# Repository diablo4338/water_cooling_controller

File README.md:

# PC Water Cooling Controller

An end-to-end fan controller solution built around a custom PCB and an `ESP32-C3` controller. The repository covers the full product scope: device firmware, a desktop application for Windows and Linux, PCB manufacturing files, and the bill of materials.

The controller is designed for:
- up to 4 fans;
- up to 4 `10k` thermistors.

The desktop application works over BLE and supports pairing mode, controller connection, telemetry monitoring, and cooling parameter updates. The hardware lives in `hardware/`, and the release pipeline builds a unified set of artifacts through [`.github/workflows/release.yml`](.github/workflows/release.yml).

## Repository structure
- [`firmware/`](firmware/README.md) - `ESP-IDF` firmware for `ESP32-C3`.
- [`pcwcc/`](pcwcc/README.md) - desktop GUI for Windows and Linux.
- [`hardware/`](hardware/README.md) - KiCad project, BOM, and production exports for the PCB.
- [`tests/raspberry/`](tests/raspberry/README.md) - Raspberry Pi helper for hardware integration tests.
- [`docker/`](docker/README.md) - local Docker environment for release-build verification.
- [Architecture and documentation index](docs/architecture.md)

## Release artifacts
The `scripts/make_release.sh` script and the `Release` workflow produce:
- firmware for `ESP32-C3`;
- a Linux `AppImage` for the desktop client;
- a production archive with `Gerber` and `drill` files for PCB manufacturing;
- checksums;
- the BOM is stored separately in [`hardware/production/bom/main.csv`](hardware/production/bom/main.csv).

Build details and structure notes are kept in the `README` files of the corresponding directories.

## License

This project is licensed for non-commercial use only.

Commercial use is not permitted without prior written permission from the author.

See [LICENSE](LICENSE) for details.

## Safety disclaimer

This is an experimental DIY hardware/software project. Use it at your own risk.
Incorrect wiring, firmware, configuration, or installation may cause hardware
damage, overheating, fire, or injury.

See [DISCLAIMER.md](DISCLAIMER.md).

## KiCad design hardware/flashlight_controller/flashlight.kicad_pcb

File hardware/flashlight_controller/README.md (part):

# Flashlight controller — revision 1.1

Рабочий проект: `flashlight.kicad_pro`, схема `flashlight.kicad_sch`, плата
`flashlight.kicad_pcb`. Исходная версия сохранена в
`revision_backup_20260924.zip`. Монтаж снизу, питание 2S 6–8,4 В,
лампа около 1 А. Генераторы находятся в `tools/`.

## Повторное использование компонентов

Референс: `U:/plate_schemas/speed_and_temp_v8`, все восемь переданных файлов
доступны. Перечень компонентов всех листов сохранён в `tools/reference_parts.json`.
Скопированные посадочные места автономны: для повторной сборки проекта диск U:
не нужен.

| Здесь | Референс | Решение |
|---|---|---|
| U1 | esp U1 | Тот же ESP32-C3-WROOM-02 |
| U2 | fan_power U5 | Тот же MCP16331T-E/CH |
| U3 | power U2 | TPS7A02-3.3 (TPS7A0233PDBVR), SOT-23-5, как в референсе |
| C10, C11 | power C6, C5 | 1 мкФ на входе и 4,7 мкФ на выходе LDO, 0805 |
| U4 | ina U6 | Тот же INA226, корпус 3×3 мм с шагом 0,5 мм |
| Q1 | fan_power Q1 | MMFTP3334K вместо AO3401A, G1/S2/D3 |
| Q2 | fan_power Q2, esp Q3 | NXV40UNR вместо 2N7002, G1/S2/D3 |
| R1 | ina R17 | WSL2512R0470FEA, 47 мОм / 1% / 1 Вт |
| D1 | fan_power D2 | PD3S120LQ, скопировано посадочное место PowerDI323 |
| D2 | fan_power D3 | 1N4148WS-HG3_A-08 |
| SW1, SW2 | esp SW1–SW3 | Скопировано посадочное место кнопок |
| R2, R8 | fan_power R29, R34 | 61,9 кОм и 100 кОм из референса |
| R3–R6, R9–R16, R18 | разные листы | Повторно используются номиналы 1 кОм, 100 кОм, 10 Ом, 10 кОм, 4,7 кОм |
| C2–C7, C10, C12–C16 | разные листы | 100 нФ, 1 мкФ и 10 мкФ в 0805; напряжение и диэлектрик по BOM |

Новые номиналы: R7 523 кОм, R17 12,4 кОм. Сохранены конденсаторы 22 мкФ,
470 мкФ и дроссель 22 мкГн: они выбраны для этого источника и нагрузки.
SRN4018-100M из референса имеет 10 мкГн; без проверки устойчивости и пульсаций
его не подставляем вместо рекомендованных для 5 В 22 мкГн.
Установлен TPS7A02-3.3 из референса: IN и EN подключены к 5 В, NC оставлен
неподключённым. Его номинальный выходной ток — 200 мА; работу ESP32-C3 с радио
нужно проверить на прототипе по просадке 3,3 В. ADS1115 не требуется для
одного термодатчика. Разъёмы SATA и вентиляторов не соответствуют назначению платы.

## Делители и потребление

R7/R8: **523 кОм / 100 кОм**, вместо 52,3 кОм / 10 кОм.
При VFB = 0,8 В выход 4,984 В, ток делителя 8 мкА вместо 80 мкА.
При типичном токе входа FB 3 нА добавочная ошибка выхода около 1,57 мВ.
Максимальный ток FB производитель не гарантирует, поэтому 100 кОм снизу —
выбранный инженерный предел, а не паспортный максимум. Увеличение ещё на порядок
без измерений неоправданно. Для 1% резисторов и диапазона VFB 0,784–0,816 В
статический диапазон примерно 4,803–5,170 В без учёта входного тока FB.
На прототипе проверить запуск, пульсации и скачки нагрузки при 6 и 8,4 В.

R2 = 61,9 кОм снижает постоянный ток включённого ключа примерно до
95–134 мкА. Увеличение до мегомов ограничено утечкой защищённого затвора
MMFTP3334K: 10 мкА плюс утечка Q2 1 мкА дали бы 0,681 В на 61,9 кОм.
Это оценка по указанным в паспортах условиям, не гарантия при любой температуре.
Ключ предназначен для медленного включения/выключения лампы; высокочастотный PWM
с резистивным выключением затвора не проверен.

Напряжение аккумулятора измеряет VBUS INA226 непосредственно; отдельного
постоянно включённого делителя батареи нет. Шунт 47 мОм даёт 47 мВ и 47 мВт
при 1 А. Диапазон INA226 ±81,92 мВ соответствует ±1,743 А **общего** тока,
включая электронику; выше этого измерение насыщается.
Для Current_LSB = 100 мкА регистр CAL = round(0,00512 / (0,0001 × 0,047)) = 1089.
Прошивку с прежними 20 мОм использовать без изменения калибровки нельзя.

Экономия на делителях не означает микроамперного сна всей платы:
включённый MCP16331 сам потребляет типично около 1 мА. INA226 также следует
переводить в power-down между измерениями, если требуется экономичный режим.

## АЦП и термодатчик

**Предварительное допущение: NTC 10 кОм при 25 °C, B3950, диапазон 0…100 °C.**
Фактический датчик и его допуски ещё нужно подтвердить. Выбранный номинал R17
нельзя считать окончательным для неизвестного датчика или отрицательных температур.

Используется GPIO0 / ADC1_CH0. GPIO1 / TEMP_EXCITE питает делитель только
на время измерения. R17 = 12,4 кОм; R18 = 1 кОм; C16 = 100 нФ у входа АЦП.
Постоянное питание 3,3 В с R17 убрано. Большое сопротивление R17 при том же NTC
ухудшило бы полезный размах сигнала; выключаемое питание уменьшает средний ток
без этого ухудшения.

| Температура | Сопротивление NTC, примерно | Напряжение АЦП при 3,3 В |
|---|---|---|
| 0 °C | 33,62 кОм | 2,411 В |
| 25 °C | 10 кОм | 1,473 В |
| 100 °C | 697,5 Ом | 0,176 В |

Размах 2,235 В использует около 89% диапазона 0…2,5 В.
Верхняя точка оставляет запас до насыщения, но после получения допусков датчика
нужен окончательный worst-case расчёт. При обрыве NTC вход поднимается к 3,3 В:
это насыщение измерителя; прошивка должна считать такой результат неисправностью,
а не температурой. При коротком замыкании вход близок к нулю.

Последовательность будущей прошивки:

1. Настроить ADC1_CH0 на ATTEN3 (`ADC_ATTEN_DB_12`; старое имя `ADC_ATTEN_DB_11`),
   включить поддерживаемую ESP-IDF калибровку.
2. Установить GPIO1 в высокий уровень; подождать **15 мс**.
   Даже при обрыве постоянная времени (12,4 кОм + 1 кОм) × 100 нФ = 1,34 мс.
3. Отбросить первую выборку, усреднить несколько измерений, перевести результат
   в мВ через калибровочный API. Измерения редкие, не поток 100 квыб/с.
4. Установить GPIO1 в низкий уровень до следующего измерения, в том числе перед сном.
5. Рассчитать Rntc = 12400 × Vadc / (Vexcite − Vadc), затем
   T = 1 / (1/298,15 + ln(Rntc/10000)/3950) − 273,15.
   Использовать измеренное/откалиброванное Vexcite: напряжение GPIO не идеальные 3,3 В.

Ток при 25 °C во время измерения около 147 мкА. При включении на 20 мс раз
в секунду среднее потребление делителя около 2,95 мкА; токи утечки сюда не включены.
Для C16 100 нФ обеспечен локальный запас заряда SAR и фильтрация; буфер для этой
редкой выборки не установлен. Итоговую погрешность проверить на известных
сопротивлениях с фактической частотой выборки и работающим радио. 12 бит не означают
12 бит абсолютной точности: для ATTEN3 паспортная ошибка после калибровки ±35 мВ
при оговорённых условиях, что особенно заметно на горячем конце NTC.

## Плата и проверки

В генераторе убраны отверстия в центральном паде ESP32. Трассировщик запрещает
via на любых падах, включая площадки той же цепи. Минимальный зазор между краем
кольца via и прямоугольником, охватывающим медь пада, — 0,15 мм.
`tools/verify_design.py` проверяет геометрию итогового файла, включая тепловые via,
и соответствие экспортированного netlist спецификации соединений.
Отчёты: `erc.rpt`, `drc.json`, `verification.json`.

Для генерации запустить `tools/build_project.py`, `tools/route_board.py`,
`tools/finish_board.py`, затем KiCad CLI ERC, DRC с `--refill-zones --save-board`,
экспорт XML netlist и `tools/verify_design.py`. Использовать настроенный Python SDK.
`tools/import_reference.py` нужен только для повторного импорта оригиналов.

## Документация производителей

- [ESP32-C3 datasheet, ADC и потребление](https://documentation.espressif.com/ESP32-C3_Datasheet_en.pdf)
- [Espressif: схема и вход АЦП](https://docs.espressif.com/projects/esp-hardware-design-guidelines/en/latest/esp32c3/schematic-checklist.html)
- [ESP-IDF: ADC](https://docs.espressif.com/projects/esp-idf/en/latest/esp32c3/api-reference/peripherals/adc/index.html)
- [MCP16331, раздел 5.2 и характеристики](https://ww1.microchip.com/downloads/en/DeviceDoc/MCP16331-Data-Sheet-20005308.pdf)
- [MMFTP3334K](https://diotec.com/files/diotec/productfiles/datasheet/mmftp3334k.pdf)
- [NXV40UN](https://assets.nexperia.com/documents/data-sheet/NXV40UN.pdf)
- [PD3S120LQ](https://www.diodes.com/datasheet/download/PD3S120LQ.pdf)
- [TPS7A02](https://www.ti.com/product/TPS7A02)
- [SRN4018](https://www.bourns.com/docs/product-datasheets/srn4018.pdf)
- [INA226](https://www.ti.com/lit/ds/symlink/ina226.pdf)

## Compact revision 0.3 (2026-11-16)

Board outline: 65 x 55.25 mm, previously 75 x 65 mm (26.3% less area).
The ESP32 antenna still overhangs the top edge; these dimensions describe the PCB.
All component packages and four mounting holes are retained. Mounting coordinates changed.
PACK_PLUS / SYS_PLUS / LAMP_PLUS use 2 mm tracks with local SOT-23 necks.
INA226 inputs use separate sense branches; the buck switching loop remains on B.Cu.
Noise and power loss have not been measured on physical hardware.

J5: two 2 x 2 mm SMD solder pads, 3 mm pitch. Pad 1 = GYRO_SIGNAL / GPIO7
(module pin 6); pad 2 = GND. For a contact switching to ground, configure an input
with a pull-up in firmware. Active outputs must use 3.3 V logic. No sensor supply
is provided on J5.

Current production exports: `fabrication_rev03/`. The previous `gerber/` directory
belongs to the old layout. Updated generators are in `tools/`.
Checks: `erc.rpt`, `drc.json`, `verification.json`.

## Two-sided block layout, revision 0.4 (2026-11-16)

Current PCB outline: **42 x 44 mm**, area 1848 mm2. This is 48.5% smaller than
revision 0.3 (65 x 55.25 mm) and 62.1% smaller than the original 75 x 65 mm.
The antenna still overhangs the upper edge. Four 3.2 mm mounting holes are retained,
with new centres (mm, top view): H1 (2, 12.8), H2 (39, 3), H3 (3, 41), H4 (40, 35.3).

B.Cu: ESP32 module, buck switching loop, shunt, lamp MOSFET, bulk capacitor and
battery/lamp contacts. F.Cu: INA226 and its input filter, LDO, buttons, gate-drive
passives, UART and sensor solder pads. The analogue block lies above the power
area on the other face, away from the buck SW node. Existing component packages
and circuit values are retained. Main battery/lamp copper remains 2 mm wide,
with local necks at device pads. Low-current signals use 0.15 mm tracks.
Both faces require assembly. Electrical noise and temperature require prototype
measurements; DRC alone does not evaluate them.

J5 is on F.Cu at (5, 34): pad 1 SIG = GPIO7, pad 2 GND, 2 x 2 mm pads at 3 mm pitch.
The signal is still 3.3 V logic; configure a pull-up for a contact to ground.

Use **fabrication_rev04/** for production. **fabrication_rev03/** and **gerber/**
are previous layouts. Layer previews: `previews/compact-rev04-top.svg` and
`previews/compact-rev04-bottom.svg`. `revision03_before_block_relayout.zip` preserves
the previous board and its generators.

Validation: ERC 0 violations; DRC 0 violations, 0 unconnected items, 0 schematic
parity issues. Independent geometry verification: 98 vias, none on a pad,
minimum required via annulus-to-pad gap 0.15 mm. Reports are in `erc.rpt`,
`drc.json` and `verification.json`.

## Mechanical revision 0.5 (2026-11-16)

Current outline: **42 x 56 mm**, from KiCad (0, -8) to (42, 48).
Four NPTH mounting holes, diameter 3.2 mm, now form a **38 x 31 mm rectangle**.
From the physical upper-left board corner their centres are:
H1 (2, 22), H2 (40, 22), H3 (2, 53), H4 (40, 53) mm.
KiCad coordinates: H1 (2, 14), H2 (40, 14), H3 (2, 45), H4 (40, 45).
The hole diameter is retained; screw-head and enclosure clearances must be matched
against the actual mounting hardware.

The ESP32 module, including its antenna, is fully above the base-board FR4.
The module body outline is x = 4.5..22.5, y = -5.85..14.15 mm in KiCad coordinates;
there is 2.15 mm of FR4 beyond its antenna end. The footprint antenna rule area
prohibits copper pours, tracks, vias and pads on both copper layers. The added
upper FR4 strip has no copper. Keep metal enclosure parts away from the antenna.
RF performance with FR4 under the antenna remains to be measured on the prototype;
see [Espressif module placement guidance](https://docs.espressif.com/projects/esp-hardware-design-guidelines/en/latest/esp32c3/pcb-layout-design.html#general-principles-of-pcb-layout-for-modules-positioning-a-module-on-a-base-board).

Current manufacturing outputs: **fabrication_rev05/**.
Mechanical drawing: `previews/mechanical-rev05.svg`; assembly layer views:
`previews/compact-rev05-top.svg`, `previews/compact-rev05-bottom.svg`.
Previous revision files remain historical. `revision04_before_mechanical_update.zip`
preserves the board before this update. `tools/verify_design.py` now checks the
hole rectangle, integer pitch, module support inside the outline and antenna keepout.

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
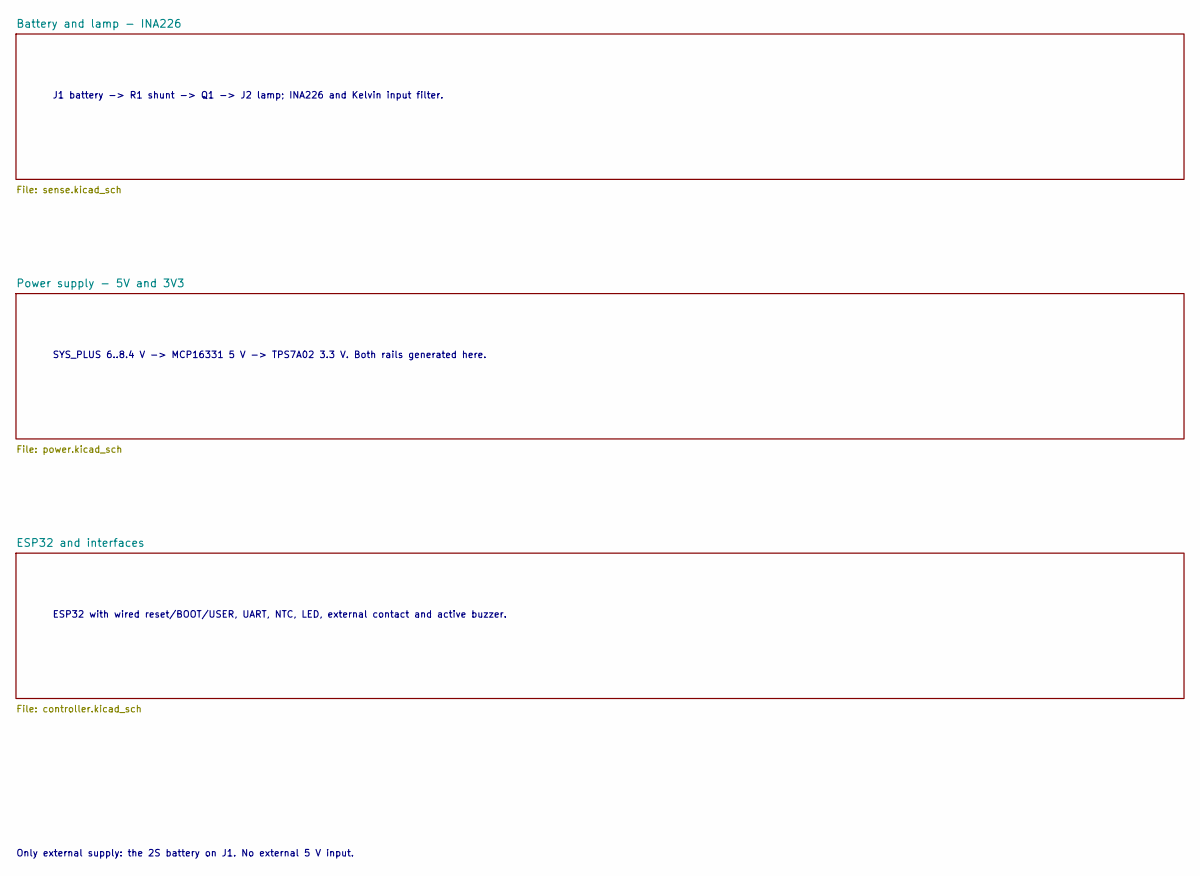
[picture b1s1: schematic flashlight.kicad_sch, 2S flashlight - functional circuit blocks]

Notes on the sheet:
SYS_PLUS 6..8.4 V -> MCP16331 5 V -> TPS7A02 3.3 V. Both rails generated here.
Only external supply: the 2S battery on J1. No external 5 V input.
ESP32 with wired reset/BOOT/USER, UART, NTC, LED, external contact and active buzzer.
J1 battery -> R1 shunt -> Q1 -> J2 lamp; INA226 and Kelvin input filter.

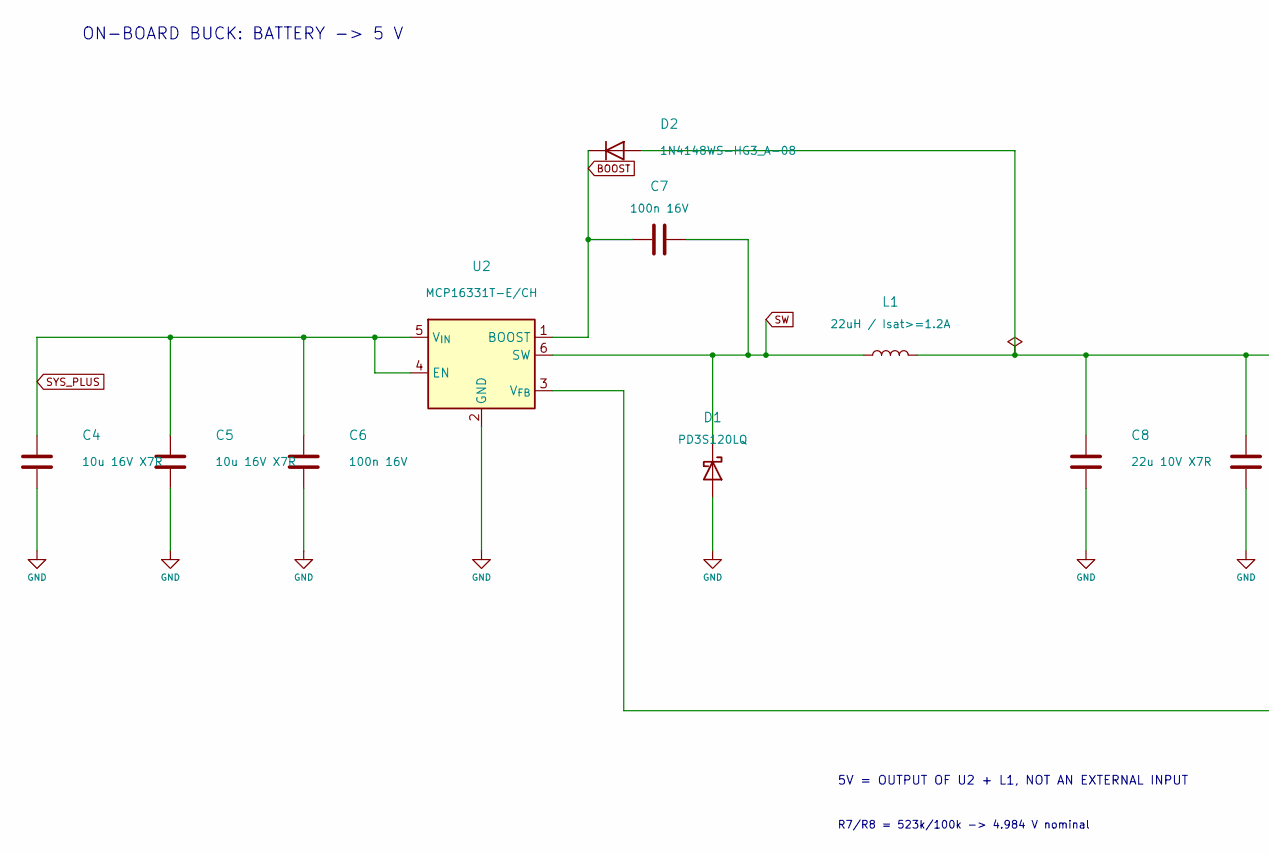
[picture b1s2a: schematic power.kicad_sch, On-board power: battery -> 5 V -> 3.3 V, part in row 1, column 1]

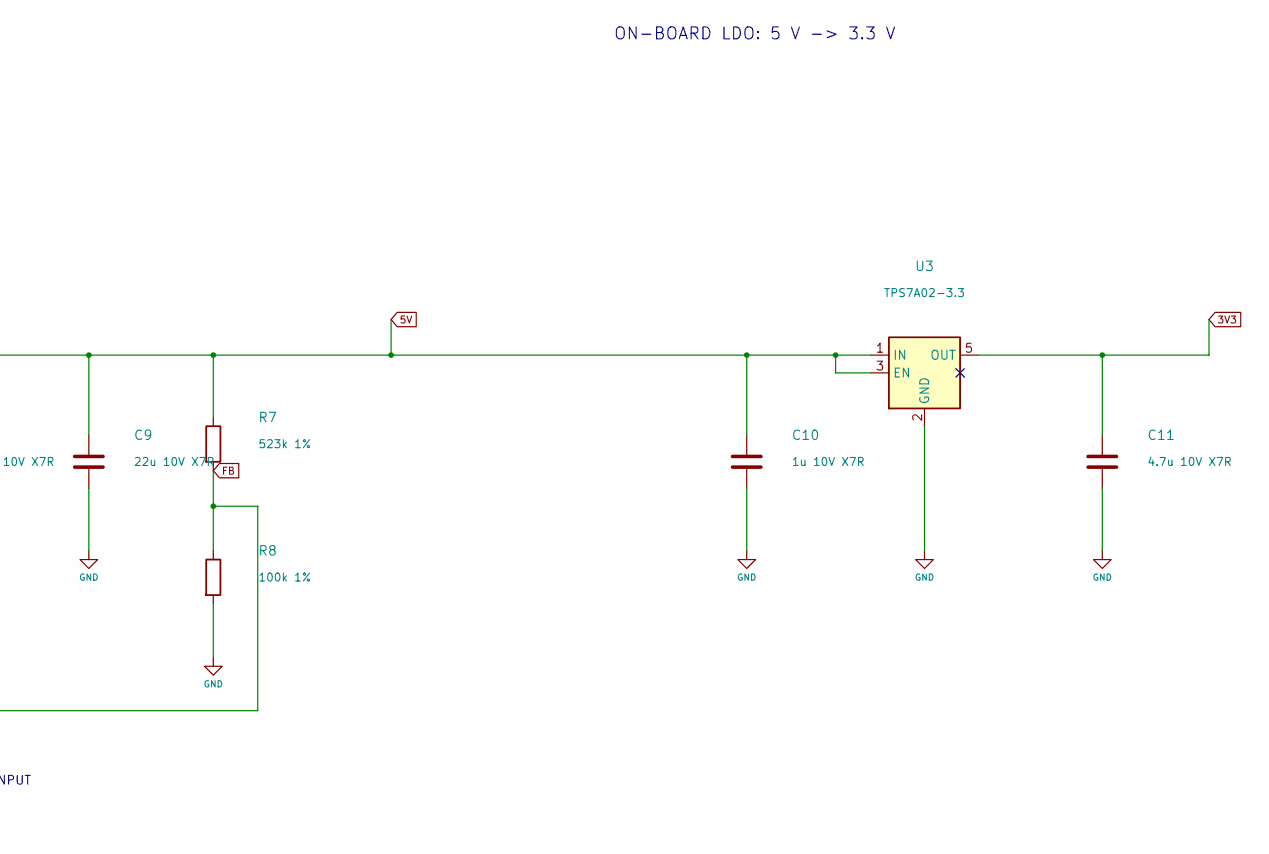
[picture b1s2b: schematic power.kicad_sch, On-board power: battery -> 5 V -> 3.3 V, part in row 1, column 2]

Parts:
C4, C5: 10u 16V X7R; C_0805_2012Metric
C6, C7: 100n 16V; C_0805_2012Metric
C8, C9: 22u 10V X7R; C_1206_3216Metric
C10: 1u 10V X7R; C_0805_2012Metric
C11: 4.7u 10V X7R; C_0805_2012Metric
D1: PD3S120LQ; Reference_PowerDI323
D2: 1N4148WS-HG3_A-08; D_SOD-323
L1: 22uH / Isat>=1.2A; L_Bourns_SRN6045TA
R7: 523k 1%; R_0805_2012Metric
R8: 100k 1%; R_0805_2012Metric
U2: MCP16331T-E/CH; SOT-23-6
U3: TPS7A02-3.3; SOT-23-5

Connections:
3V3: C11.1, U3.5 (OUT); also elsewhere on the board
5V: C8.1, C9.1, C10.1, D2.2 (A), L1.2, R7.1, U3.1 (IN), U3.3 (EN)
BOOST: C7.1, D2.1 (K), U2.1 (BOOST)
FB: R7.2, R8.1, U2.3 (V_{FB})
GND: C4.2, C5.2, C6.2, C8.2, C9.2, C10.2, C11.2, D1.2 (A), R8.2, U2.2 (GND), U3.2 (GND); also elsewhere on the board
SW: C7.2, D1.1 (K), L1.1, U2.6 (SW)
SYS_PLUS: C4.1, C5.1, C6.1, U2.4 (EN), U2.5 (V_{IN}); also elsewhere on the board

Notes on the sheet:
5V = OUTPUT OF U2 + L1, NOT AN EXTERNAL INPUT
R7/R8 = 523k/100k -> 4.984 V nominal
ON-BOARD BUCK: BATTERY -> 5 V
ON-BOARD LDO: 5 V -> 3.3 V

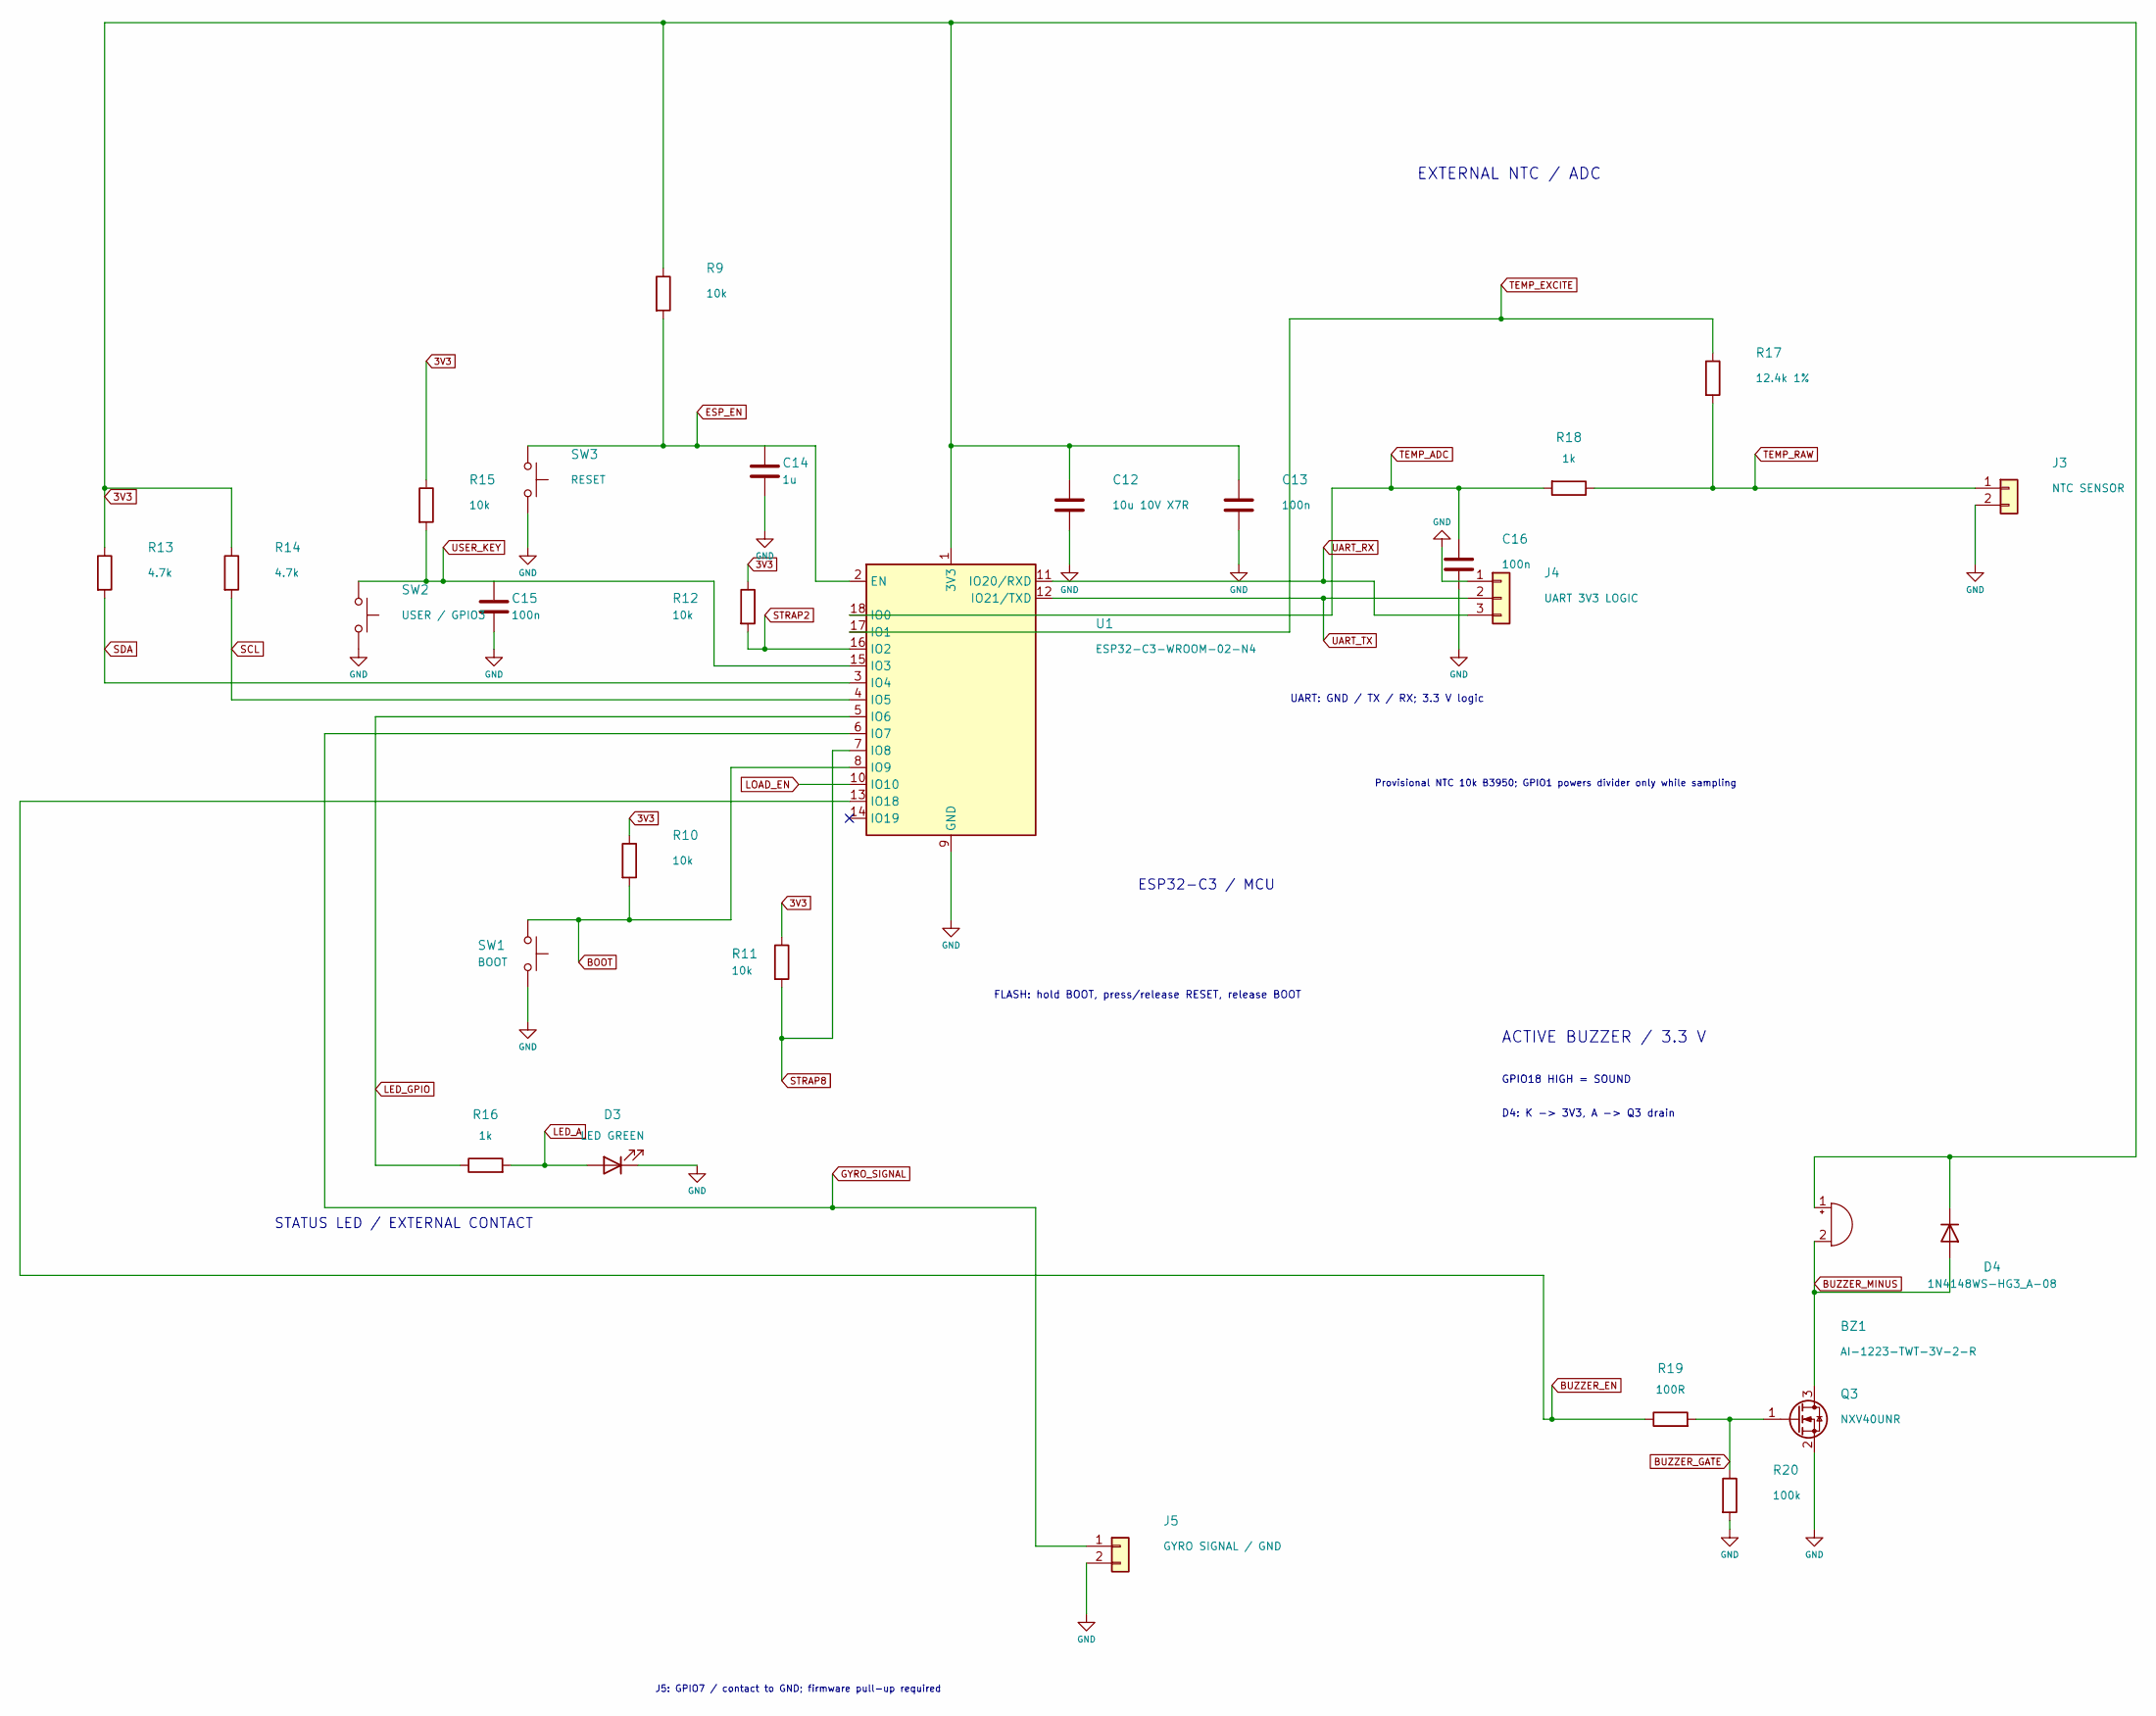
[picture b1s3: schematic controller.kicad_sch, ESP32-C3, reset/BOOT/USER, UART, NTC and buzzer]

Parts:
BZ1: AI-1223-TWT-3V-2-R; Buzzer_12x9.5RM7.6
C12: 10u 10V X7R; C_0805_2012Metric
C13, C15, C16: 100n; C_0805_2012Metric
C14: 1u; C_0805_2012Metric
D3: LED GREEN; LED_0805_2012Metric
D4: 1N4148WS-HG3_A-08; D_SOD-323
J3: NTC SENSOR; SensorPads_2
J4: UART 3V3 LOGIC; UART_Pads_3
J5: GYRO SIGNAL / GND; GyroPads_2
Q3: NXV40UNR; SOT-23
R9, R10, R11, R12, R15: 10k; R_0805_2012Metric
R13, R14: 4.7k; R_0805_2012Metric
R16, R18: 1k; R_0805_2012Metric
R17: 12.4k 1%; R_0805_2012Metric
R19: 100R; R_0805_2012Metric
R20: 100k; R_0805_2012Metric
SW1: BOOT; Reference_Button
SW2: USER / GPIO3; Reference_Button
SW3: RESET; Reference_Button
U1: ESP32-C3-WROOM-02-N4; ESP32-C3-WROOM-02

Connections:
3V3: BZ1.1 (+), C12.1, C13.1, D4.1 (K), R9.1, R10.1, R11.1, R12.1, R13.1, R14.1, R15.1, U1.1 (3V3); also elsewhere on the board
BOOT: R10.2, SW1.1, U1.8 (IO9)
BUZZER_EN: R19.1, U1.13 (IO18)
BUZZER_GATE: Q3.1 (G), R19.2, R20.1
BUZZER_MINUS: BZ1.2 (-), D4.2 (A), Q3.3 (D)
ESP_EN: C14.1, R9.2, SW3.1, U1.2 (EN)
GND: C12.2, C13.2, C14.2, C15.2, C16.2, D3.1 (K), J3.2, J4.1, J5.2, Q3.2 (S), R20.2, SW1.2, SW2.2, SW3.2, U1.9 (GND), U1.19 (GND); also elsewhere on the board
GYRO_SIGNAL: J5.1, U1.6 (IO7)
LED_A: D3.2 (A), R16.2
LED_GPIO: R16.1, U1.5 (IO6)
LOAD_EN: U1.10 (IO10); also elsewhere on the board
SCL: R14.2, U1.4 (IO5); also elsewhere on the board
SDA: R13.2, U1.3 (IO4); also elsewhere on the board
STRAP2: R12.2, U1.16 (IO2)
STRAP8: R11.2, U1.7 (IO8)
TEMP_ADC: C16.1, R18.2, U1.18 (IO0)
TEMP_EXCITE: R17.1, U1.17 (IO1)
TEMP_RAW: J3.1, R17.2, R18.1
UART_RX: J4.3, U1.11 (IO20/RXD)
UART_TX: J4.2, U1.12 (IO21/TXD)
USER_KEY: C15.1, R15.2, SW2.1, U1.15 (IO3)

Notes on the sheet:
J5: GPIO7 / contact to GND; firmware pull-up required
ACTIVE BUZZER / 3.3 V
UART: GND / TX / RX; 3.3 V logic
D4: K -> 3V3, A -> Q3 drain
GPIO18 HIGH = SOUND
FLASH: hold BOOT, press/release RESET, release BOOT
STATUS LED / EXTERNAL CONTACT
Provisional NTC 10k B3950; GPIO1 powers divider only while sampling
ESP32-C3 / MCU
EXTERNAL NTC / ADC

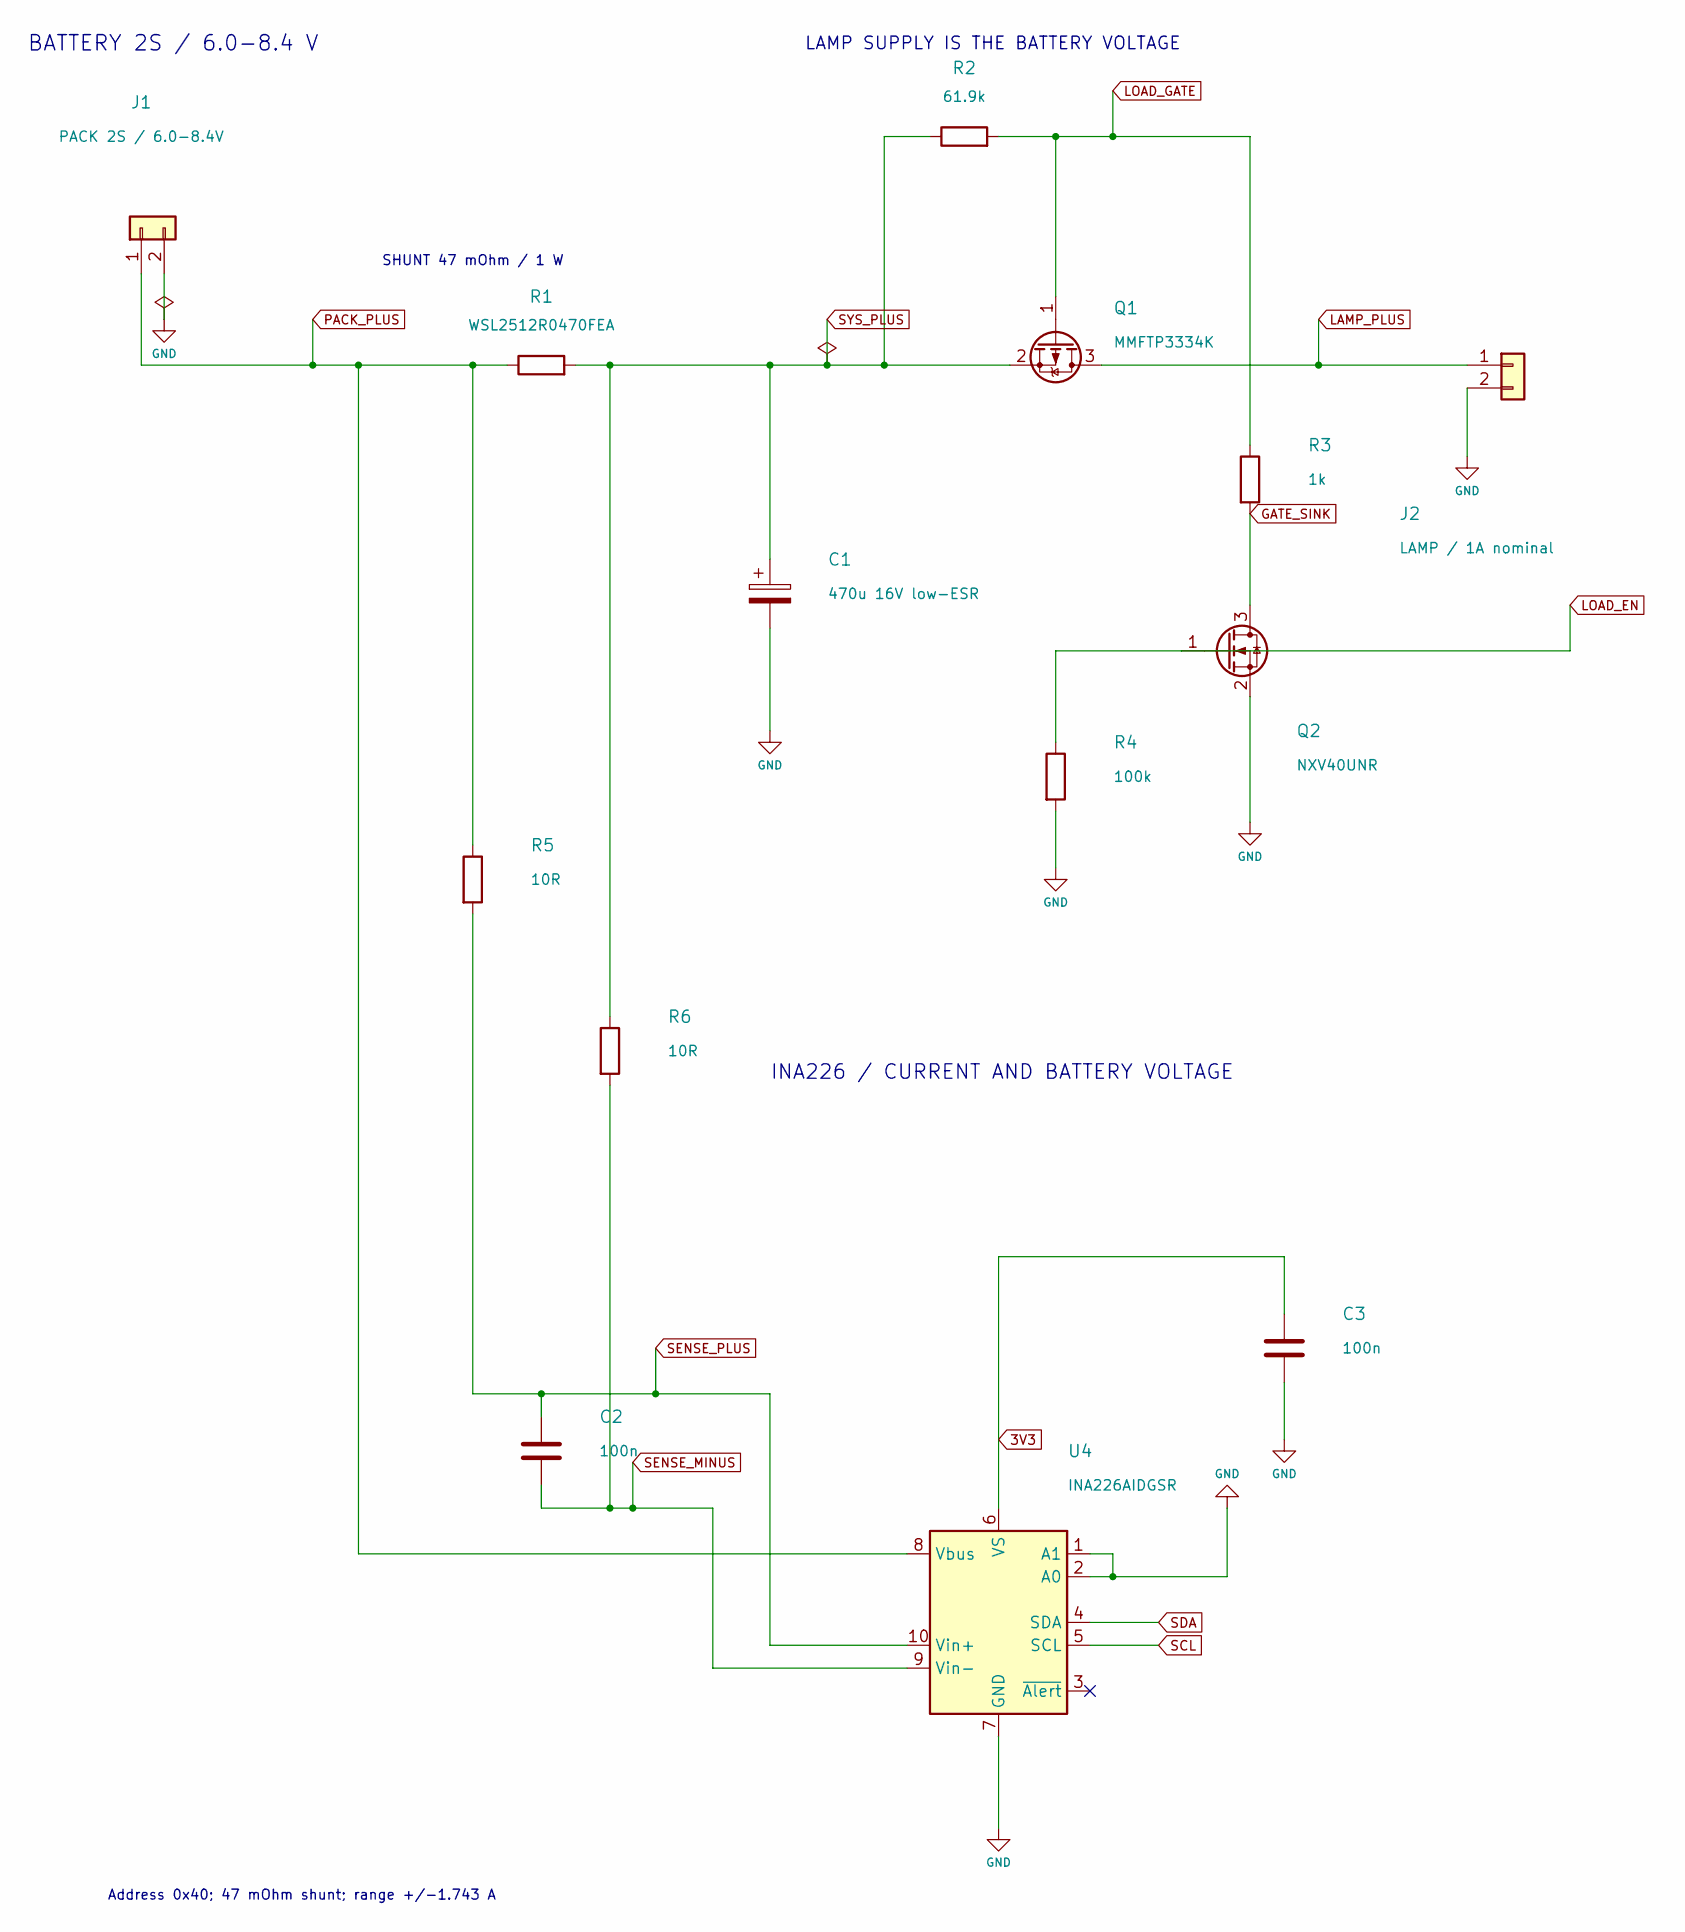
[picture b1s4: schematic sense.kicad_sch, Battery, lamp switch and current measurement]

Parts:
C1: 470u 16V low-ESR; Electrolytic_D10_P5
C2, C3: 100n; C_0805_2012Metric
J1: PACK 2S / 6.0-8.4V; WirePads_2x_5mm
J2: LAMP / 1A nominal; WirePads_2x_5mm
Q1: MMFTP3334K; SOT-23
Q2: NXV40UNR; SOT-23
R1: WSL2512R0470FEA; R_2512_6332Metric
R2: 61.9k; R_0805_2012Metric
R3: 1k; R_0805_2012Metric
R4: 100k; R_0805_2012Metric
R5, R6: 10R; R_0805_2012Metric
U4: INA226AIDGSR; MSOP-10_3x3mm_P0.5mm

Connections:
3V3: C3.1, U4.6 (VS); also elsewhere on the board
GATE_SINK: Q2.3 (D), R3.2
GND: C1.2, C3.2, J1.2, J2.2, Q2.2 (S), R4.2, U4.1 (A1), U4.2 (A0), U4.7 (GND); also elsewhere on the board
LAMP_PLUS: J2.1, Q1.3 (D)
LOAD_EN: Q2.1 (G), R4.1; also elsewhere on the board
LOAD_GATE: Q1.1 (G), R2.2, R3.1
PACK_PLUS: J1.1, R1.1, R5.1, U4.8 (Vbus)
SCL: U4.5 (SCL); also elsewhere on the board
SDA: U4.4 (SDA); also elsewhere on the board
SENSE_MINUS: C2.2, R6.2, U4.9 (Vin-)
SENSE_PLUS: C2.1, R5.2, U4.10 (Vin+)
SYS_PLUS: C1.1, Q1.2 (S), R1.2, R2.1, R6.1; also elsewhere on the board

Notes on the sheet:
SHUNT 47 mOhm / 1 W
Address 0x40; 47 mOhm shunt; range +/-1.743 A
BATTERY 2S / 6.0-8.4 V
LAMP SUPPLY IS THE BATTERY VOLTAGE
INA226 / CURRENT AND BATTERY VOLTAGE

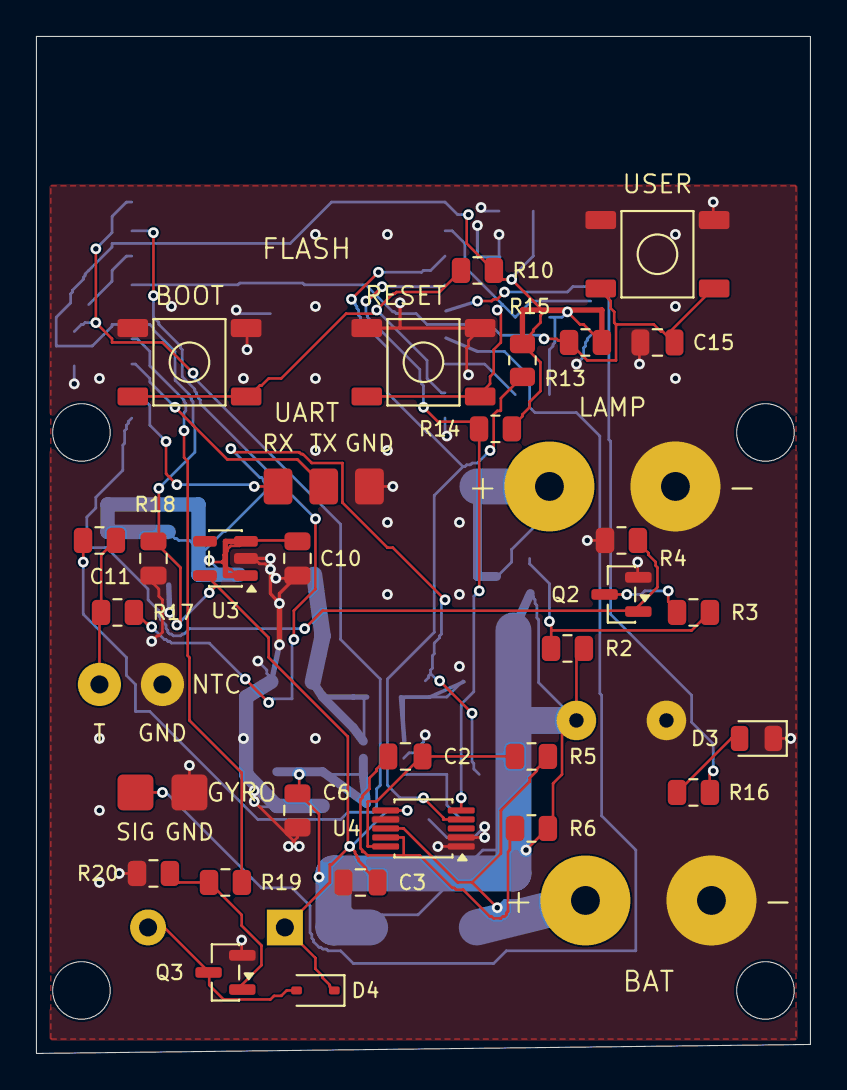
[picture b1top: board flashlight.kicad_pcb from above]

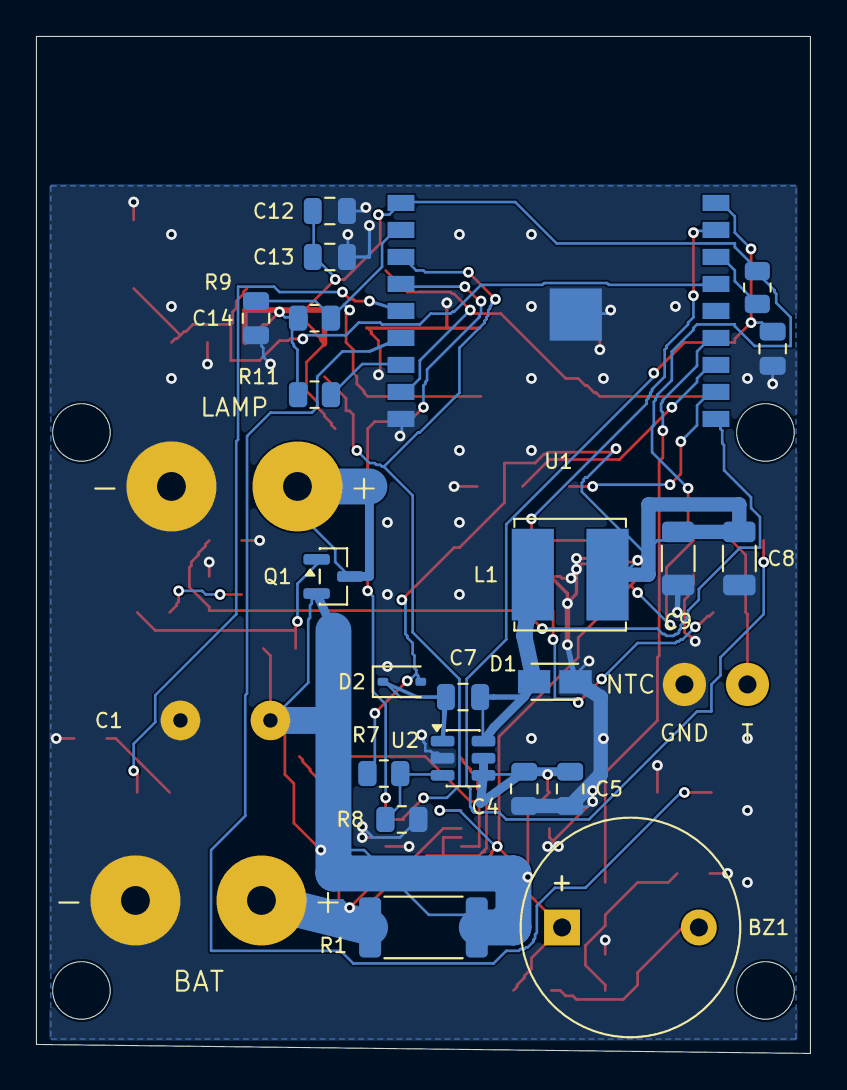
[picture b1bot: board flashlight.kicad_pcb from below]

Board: 2 copper layers, 43.0 x 56.5 mm, 61 parts (30 on the bottom side), 32 nets.

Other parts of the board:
H1, H2, H3, H4: MountingHole_3.2mm

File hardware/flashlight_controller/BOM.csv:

Reference,Value,Footprint,Notes
J1,PACK 2S / 6.0-8.4V,Flashlight:WirePads_2x_5mm,
J2,LAMP / 1A nominal,Flashlight:WirePads_2x_5mm,
R1,WSL2512R0470FEA,Flashlight:R_2512_6332Metric,Reference ina R17; 47mOhm 1% 1W; INA226 full scale 1.743A; update calibration
Q1,MMFTP3334K,Flashlight:SOT-23,"Reference fan_power Q1; verified G1 S2 D3; slow lamp on/off, not high-frequency PWM"
Q2,NXV40UNR,Flashlight:SOT-23,Reference fan_power Q2 / esp Q3; verified G1 S2 D3
R2,61.9k,Flashlight:R_0805_2012Metric,Reference 61k9; 11uA combined gate/sink leakage gives 0.681V off-state Vgs
R3,1k,Flashlight:R_0805_2012Metric,
R4,100k,Flashlight:R_0805_2012Metric,
C1,470u 16V low-ESR,Flashlight:Electrolytic_D10_P5,Bulk buffer for lamp pulses; mounted on bottom
U4,INA226AIDGSR,Flashlight:MSOP-10_3x3mm_P0.5mm,I2C address 0x40; VBUS senses raw pack voltage
R5,10R,Flashlight:R_0805_2012Metric,
R6,10R,Flashlight:R_0805_2012Metric,
C2,100n,Flashlight:C_0805_2012Metric,
C3,100n,Flashlight:C_0805_2012Metric,
U2,MCP16331T-E/CH,Flashlight:SOT-23-6,
C4,10u 16V X7R,Flashlight:C_0805_2012Metric,
C5,10u 16V X7R,Flashlight:C_0805_2012Metric,
C6,100n 16V,Flashlight:C_0805_2012Metric,
D1,PD3S120LQ,Flashlight:Reference_PowerDI323,"Reference fan_power D2; 20V 1A; cathode SW, anode GND"
L1,22uH / Isat>=1.2A,Flashlight:L_Bourns_SRN6045TA,SRN6045TA-220M or electrically equivalent footprint-compatible part
C7,100n 16V,Flashlight:C_0805_2012Metric,
D2,1N4148WS-HG3_A-08,Flashlight:D_SOD-323,"Reference fan_power D3; cathode BOOST, anode 5V"
C8,22u 10V X7R,Flashlight:C_1206_3216Metric,
C9,22u 10V X7R,Flashlight:C_1206_3216Metric,
R7,523k 1%,Flashlight:R_0805_2012Metric,Feedback current 8uA; verify stability on assembled board
R8,100k 1%,Flashlight:R_0805_2012Metric,"Reference 100k; practical design ceiling, no manufacturer maximum specified"
U3,TPS7A02-3.3,Flashlight:SOT-23-5,Reference power U2; TPS7A0233PDBVR; IN1 GND2 EN3 NC4 OUT5; rated 200mA
C10,1u 10V X7R,Flashlight:C_0805_2012Metric,Reference power C6; local LDO input bypass
C11,4.7u 10V X7R,Flashlight:C_0805_2012Metric,Reference power C5; local LDO output bypass
U1,ESP32-C3-WROOM-02-N4,Flashlight:ESP32-C3-WROOM-02,"GPIO0 ADC1_CH0, GPIO1 switched NTC excitation; antenna above FR4; all-layer copper keepout"
C12,10u 10V X7R,Flashlight:C_0805_2012Metric,
C13,100n,Flashlight:C_0805_2012Metric,
R9,10k,Flashlight:R_0805_2012Metric,
C14,1u,Flashlight:C_0805_2012Metric,
R10,10k,Flashlight:R_0805_2012Metric,
R11,10k,Flashlight:R_0805_2012Metric,
R12,10k,Flashlight:R_0805_2012Metric,
R13,4.7k,Flashlight:R_0805_2012Metric,
R14,4.7k,Flashlight:R_0805_2012Metric,
SW1,BOOT,Flashlight:Reference_Button,Reference esp button footprint
SW2,USER / GPIO3,Flashlight:Reference_Button,Reference esp button footprint
R15,10k,Flashlight:R_0805_2012Metric,
C15,100n,Flashlight:C_0805_2012Metric,
D3,LED GREEN,Flashlight:LED_0805_2012Metric,
R16,1k,Flashlight:R_0805_2012Metric,
J3,NTC SENSOR,Flashlight:SensorPads_2,"External NTC to ground; provisional 10k/B3950, confirm actual sensor"
R17,12.4k 1%,Flashlight:R_0805_2012Metric,Provisional NTC10k B3950 0..100C; GPIO1 high during sampling only; settle 15ms
R18,1k,Flashlight:R_0805_2012Metric,
C16,100n,Flashlight:C_0805_2012Metric,
J4,UART 3V3 LOGIC,Flashlight:UART_Pads_3,"Only GND, MCU TX and MCU RX; 3.3V logic; power board from pack; use BOOT and RESET buttons for download mode"
J5,GYRO SIGNAL / GND,Flashlight:GyroPads_2,"GPIO7 input (module pad6), 3.3V logic; contact to GND requires firmware pull-up"
BZ1,AI-1223-TWT-3V-2-R,Flashlight:Buzzer_12x9.5RM7.6,"Active magnetic 3V indicator; 2..4V; <=30mA at 3V; diameter12, pitch7.6; GPIO18 high=ON"
Q3,NXV40UNR,Flashlight:SOT-23,NXV40UNR G1 S2 D3; low-side buzzer driver
R19,100R,Flashlight:R_0805_2012Metric,Series gate resistor; not a pull resistor
R20,100k,Flashlight:R_0805_2012Metric,Gate-source pull-down; default OFF
D4,1N4148WS-HG3_A-08,Flashlight:D_SOD-323,"Clamp diode, cathode to 3V3, anode to buzzer minus"
SW3,RESET,Flashlight:Reference_Button,Momentary reset: EN to GND; R9=10k pull-up to3V3 and C14=1u RC retained

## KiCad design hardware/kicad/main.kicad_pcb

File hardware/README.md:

# Hardware

Hardware assets for the controller: the KiCad board project, PCB production files, and the bill of materials.

## Structure
- `kicad/` - KiCad project sources:
  - `main.kicad_pro` - project file;
  - `main.kicad_sch` - top-level schematic;
  - `main.kicad_pcb` - PCB;
  - additional schematic sheets: `ads`, `esp`, `fan_power`, `fans`, `ina`, `power`.
- `production/gerbers/` - `Gerber` files for board fabrication.
- `production/drill/` - drill files.
- `production/bom/main.csv` - BOM.
- `production/schematic-pdf/main.pdf` - schematic PDF export.

## Production artifacts
[`../scripts/build_hardware.sh`](../scripts/build_hardware.sh) builds the following archive in `dist/`:

```text
pc-water-cooling-controller-<version>-hardware-gerbers-drill.zip
```

It contains:
- all files from `production/gerbers/`;
- all files from `production/drill/`.

The BOM is kept in the repository separately and is not packed by this script, so it should be treated as an independent manufacturing artifact.

## Practical use
If the task is related to board manufacturing or revision work, this directory contains the working inputs:
- source files for schematic and PCB changes;
- ready-to-send fabrication exports;
- the current component list.

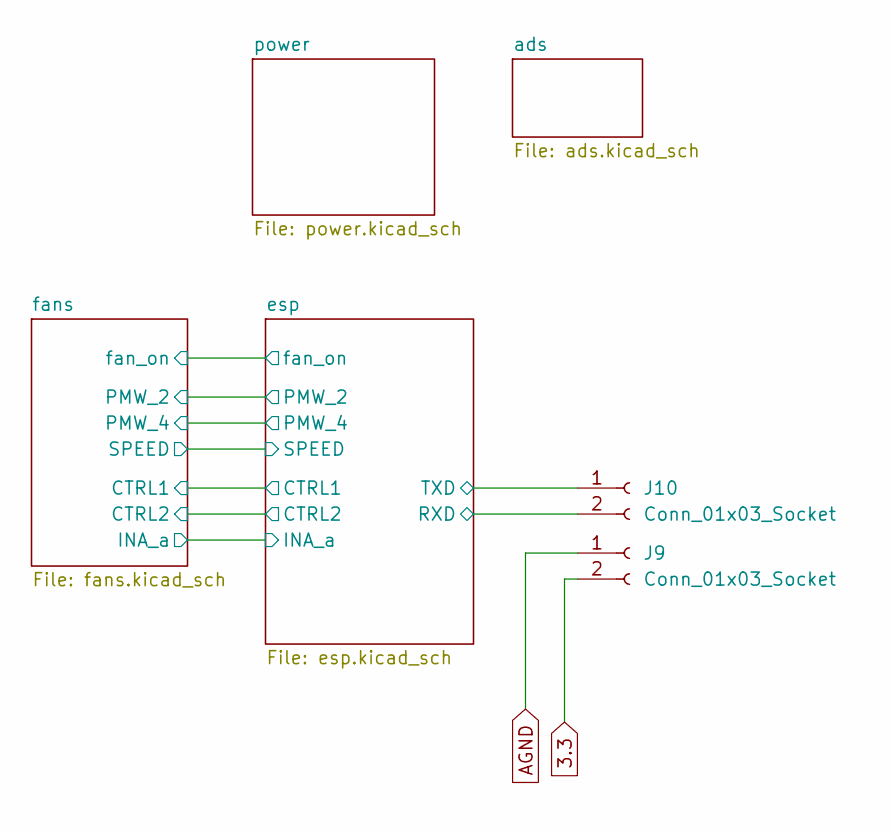
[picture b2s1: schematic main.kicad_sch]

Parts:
J9, J10: Conn_01x03_Socket; PinHeader_1x02_P2.54mm_Vertical

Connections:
3.3: J9.2; also elsewhere on the board
/esp/RXD: J10.2; also elsewhere on the board
/esp/TXD: J10.1; also elsewhere on the board
AGND: J9.1; also elsewhere on the board
